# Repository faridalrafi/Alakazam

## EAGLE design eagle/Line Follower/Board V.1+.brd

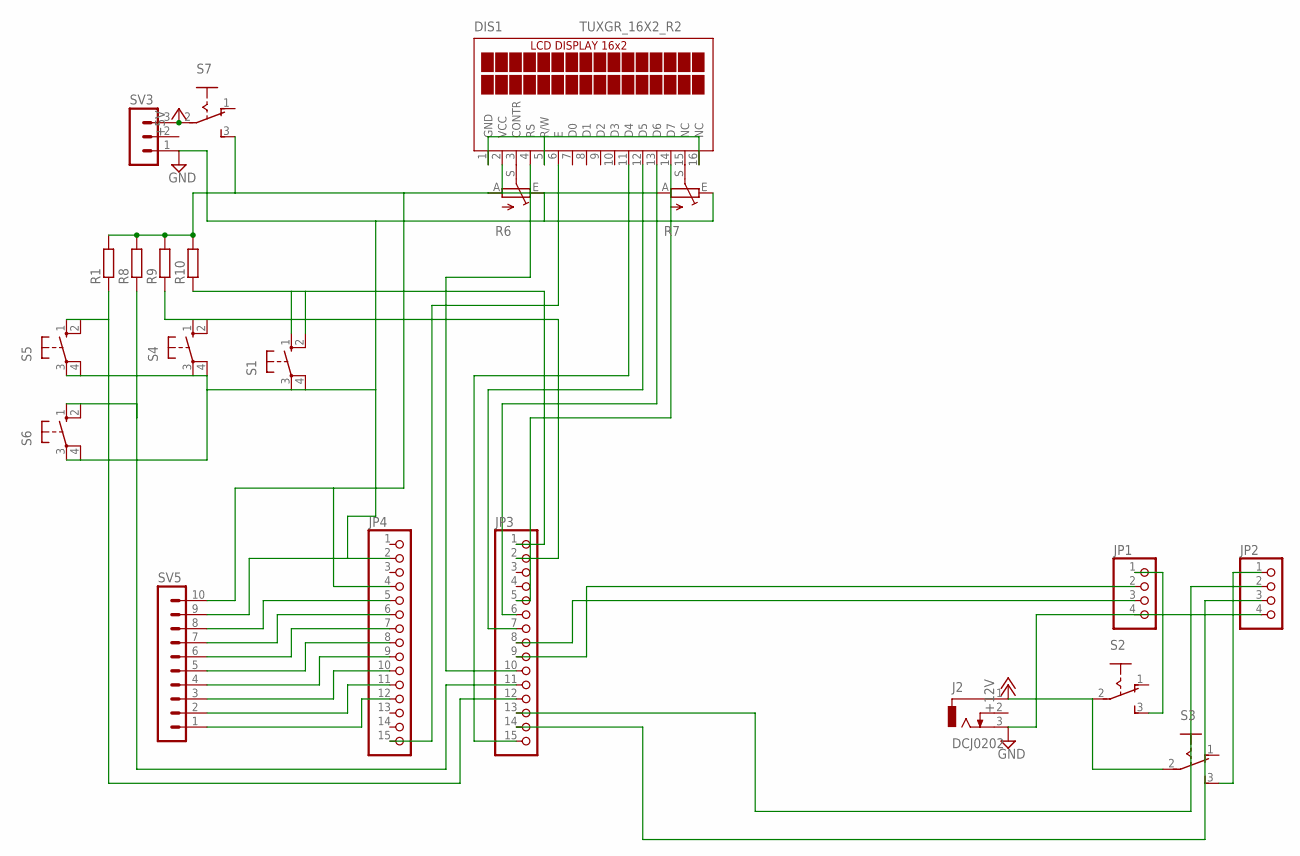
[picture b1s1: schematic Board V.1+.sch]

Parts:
DIS1: TUXGR_16X2_R2
J2: DCJ0202
JP1, JP2: PINHD-1X4; 1X04
JP3, JP4: PINHD-1X15; 1X15
R1, R8, R9, R10: R-EU_0204/7; 0204/7
R6, R7: TRIM_EU-B25P; B25P
S1, S4, S5, S6: 10-XX; B3F-10XX
S2, S3, S7: 255SB
SV3: MA03-1
SV5: MA10-1

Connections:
+5V: S7.2, SV3.3
+5V2: DIS1.2 (VCC), JP4.4, R1.2, R6.A, R7.A, R8.2, R9.2, R10.2, S7.3 (S), SV5.10
+12V: J2.1, S2.2, S3.2
GND: J2.3, JP1.4, JP2.4, JP4.2, R6.E, R7.E, S1.3, S1.4 (P1), S4.3, S4.4 (P1), S5.3, S5.4 (P1), S6.3, S6.4 (P1), SV3.1, SV5.9
unnamed: JP1.1, S2.3 (S)
unnamed: JP2.1, S3.3 (S)
unnamed: JP1.3, JP3.8
unnamed: JP1.2, JP3.9
unnamed: JP3.1, R10.1, S1.1 (S), S1.2 (S1)
unnamed: DIS1.15 (NC), R7.S
unnamed: JP2.2, JP3.13
unnamed: DIS1.4 (RS), JP3.10
unnamed: DIS1.3 (CONTR), R6.S
unnamed: DIS1.6 (E), JP4.15
unnamed: DIS1.11 (D4), JP3.15
unnamed: JP4.5, SV5.8
unnamed: JP4.6, SV5.7
unnamed: JP4.7, SV5.6
unnamed: JP4.8, SV5.5
unnamed: JP4.9, SV5.4
unnamed: DIS1.12 (D5), JP3.7
unnamed: DIS1.13 (D6), JP3.6
unnamed: DIS1.14 (D7), JP3.5
unnamed: JP3.2, R9.1, S4.1 (S), S4.2 (S1)
unnamed: JP3.11, R8.1, S6.1 (S), S6.2 (S1)
unnamed: JP3.12, R1.1, S5.1 (S), S5.2 (S1)
unnamed: DIS1.1 (GND), DIS1.5 (R/W), DIS1.16 (NC)
unnamed: JP2.3, JP3.14
unnamed: JP4.10, SV5.3
unnamed: JP4.11, SV5.2
unnamed: JP4.12, SV5.1

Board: 2 copper layers, 21 parts (1 on the bottom side), 31 nets, no tracks yet.

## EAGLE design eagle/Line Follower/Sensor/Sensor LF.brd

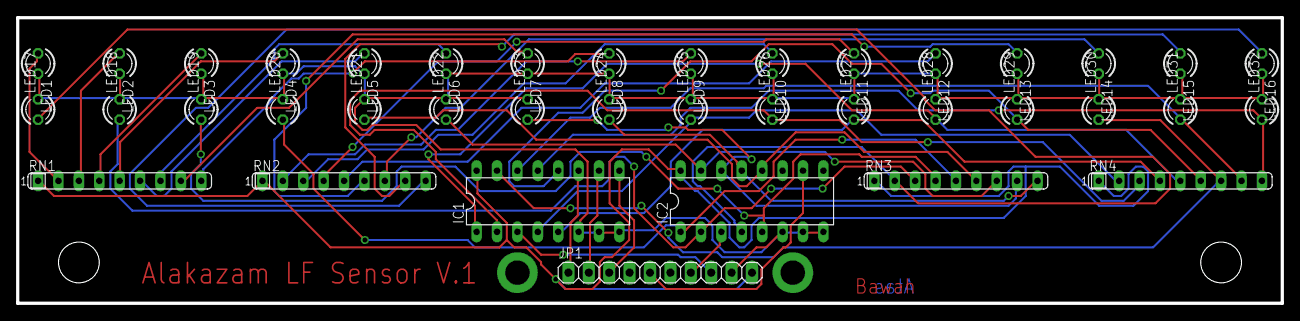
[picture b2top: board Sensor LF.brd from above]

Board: 2 copper layers, 157.5 x 35.6 mm, 39 parts (0 on the bottom side), 42 nets.

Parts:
IC1, IC2: 4051N; DIL16
JP1: 1X10
LED1, LED2, LED3, LED4, LED5, LED6, LED7, LED8, LED9, LED10, LED11, LED12, LED13, LED14, LED15, LED16, LED17, LED18, LED19, LED20, LED21, LED22, LED23, LED24, LED25, LED26, LED27, LED28, LED29, LED30, LED31, LED32: LED3MM
RN1, RN2: 220; SIL9
RN3, RN4: 10K; SIL9

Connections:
+5V: IC1.16, IC2.16, JP1.10, RN1.1, RN2.1, RN3.1, RN4.1
GND: IC1.6, IC1.7, IC1.8, IC2.6, IC2.7, IC2.8, JP1.9, LED1.K, LED2.K, LED3.K, LED4.K, LED5.K, LED6.K, LED7.K, LED8.K, LED9.K, LED10.K, LED11.K, LED12.K, LED13.K, LED14.K, LED15.K, LED16.K, LED17.K, LED18.K, LED19.K, LED20.K, LED21.K, LED22.K, LED23.K, LED24.K, LED25.K, LED26.K, LED27.K, LED28.K, LED29.K, LED30.K, LED31.K, LED32.K
unnamed: IC1.10, JP1.2
unnamed: IC1.9, JP1.3
unnamed: IC2.11, JP1.6
unnamed: IC2.10, JP1.5
unnamed: IC2.9, JP1.4
unnamed: IC2.3, JP1.7
unnamed: LED1.A, RN1.2
unnamed: LED2.A, RN1.3
unnamed: IC2.4, LED17.A, RN3.2
unnamed: IC2.2, LED18.A, RN3.3
unnamed: IC2.5, LED19.A, RN3.4
unnamed: IC2.1, LED20.A, RN3.5
unnamed: IC2.12, LED21.A, RN3.6
unnamed: IC2.15, LED22.A, RN3.7
unnamed: IC2.14, LED23.A, RN3.8
unnamed: IC2.13, LED24.A, RN3.9
unnamed: IC1.4, LED25.A, RN4.2
unnamed: IC1.2, LED26.A, RN4.3
unnamed: IC1.5, LED27.A, RN4.4
unnamed: IC1.1, LED28.A, RN4.5
unnamed: IC1.12, LED29.A, RN4.6
unnamed: IC1.15, LED30.A, RN4.7
unnamed: IC1.14, LED31.A, RN4.8
unnamed: IC1.13, LED32.A, RN4.9
unnamed: LED3.A, RN1.4
unnamed: LED4.A, RN1.5
unnamed: LED5.A, RN1.6
unnamed: LED6.A, RN1.7
unnamed: LED7.A, RN1.8
unnamed: LED8.A, RN1.9
unnamed: LED9.A, RN2.2
unnamed: LED10.A, RN2.3
unnamed: LED11.A, RN2.4
unnamed: LED12.A, RN2.5
unnamed: LED13.A, RN2.6
unnamed: LED14.A, RN2.7
unnamed: LED15.A, RN2.8
unnamed: LED16.A, RN2.9
unnamed: IC1.3, JP1.8
unnamed: IC1.11, JP1.1

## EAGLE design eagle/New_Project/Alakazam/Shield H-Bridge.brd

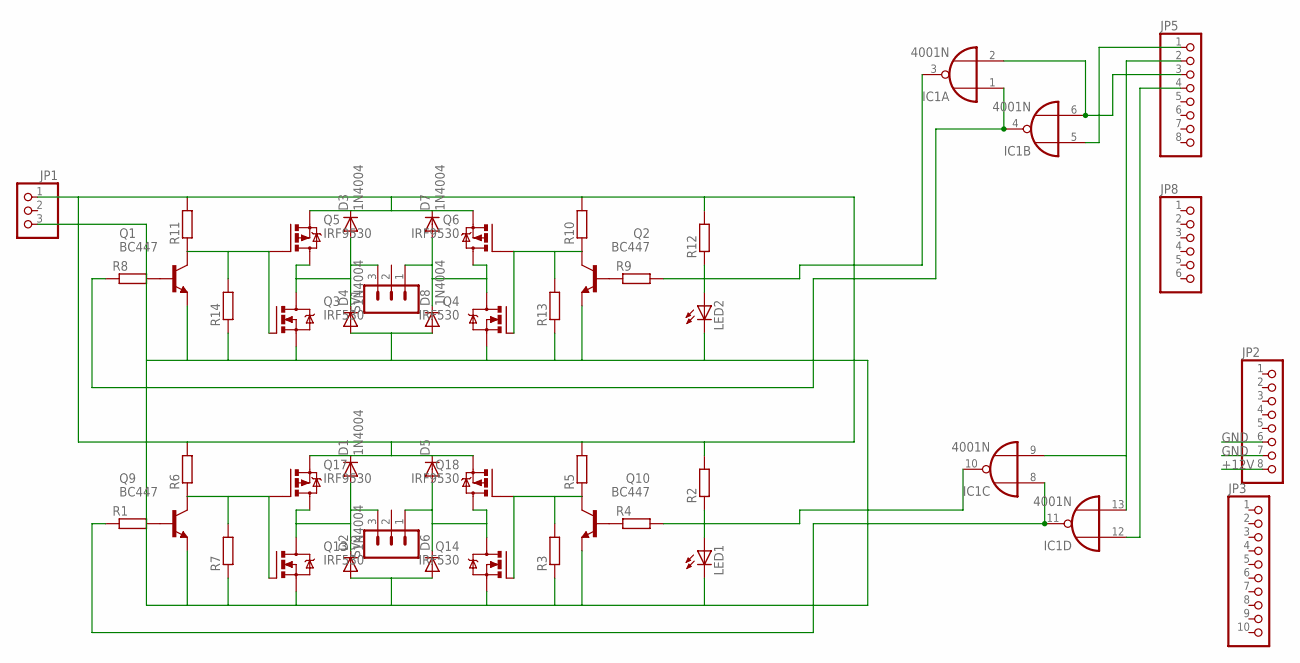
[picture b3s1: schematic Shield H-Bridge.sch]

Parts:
D1, D2, D3, D4, D5, D6, D7, D8: 1N4004; DO41-10
IC1: 4001N; DIL14
JP1: PINHD-1X3; 1X03
JP2, JP5: PINHD-1X8; 1X08
JP3: PINHD-1X10; 1X10
JP8: PINHD-1X6; 1X06
LED1, LED2: LED3MM
Q1, Q2, Q9, Q10: BC447; TO92-EBC
Q3, Q4, Q13, Q14: IRF530; TO220BV
Q5, Q6, Q17, Q18: IRF9530; TO220BV
R1, R4, R5, R6, R8, R9, R10, R11: R-EU_0207/10; 0207/10
R2, R12: R-EU_0204/5; 0204/5
R3, R7, R13, R14: R-EU_0204/7; 0204/7
SV1, SV2: MA03-1

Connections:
+12V: D1.C, D3.C, D5.C, D7.C, JP1.1, JP2.8, Q5.S, Q6.S, Q17.S, Q18.S, R2.2, R5.2, R6.2, R10.2, R11.2, R12.2
GND: D2.A, D4.A, D6.A, D8.A, JP1.3, JP2.6, JP2.7, LED1.K (C), LED2.K (C), Q1.E, Q2.E, Q3.S, Q4.S, Q9.E, Q10.E, Q13.S, Q14.S, R3.1, R7.1, R13.1, R14.1
unnamed: Q9.B, R1.2
unnamed: Q10.B, R4.1
unnamed: D7.A, D8.C, Q4.D, Q6.D, SV1.1
unnamed: IC1.12 (I0), JP5.4
unnamed: D3.A, D4.C, Q3.D, Q5.D, SV1.3
unnamed: Q2.C, Q4.G, Q6.G, R10.1, R13.2
unnamed: D5.A, D6.C, Q14.D, Q18.D, SV2.1
unnamed: D1.A, D2.C, Q13.D, Q17.D, SV2.3
unnamed: LED1.A, R2.1
unnamed: Q1.B, R8.2
unnamed: Q2.B, R9.1
unnamed: Q10.C, Q14.G, Q18.G, R3.2, R5.1
unnamed: Q1.C, Q3.G, Q5.G, R11.1, R14.2
unnamed: LED2.A, R12.1
unnamed: IC1.2 (I1), IC1.6 (I1), JP5.3
unnamed: Q9.C, Q13.G, Q17.G, R6.1, R7.2
unnamed: IC1.9 (I1), IC1.13 (I1), JP5.2
unnamed: IC1.5 (I0), JP5.1
PWM1: IC1.10 (O), R4.2
PWM2: IC1.8 (I0), IC1.11 (O), R1.1
PWM3: IC1.1 (I0), IC1.4 (O), R8.1
PWM4: IC1.3 (O), R9.2
VDD: IC1.14 (VDD)
VSS: IC1.7 (VSS)

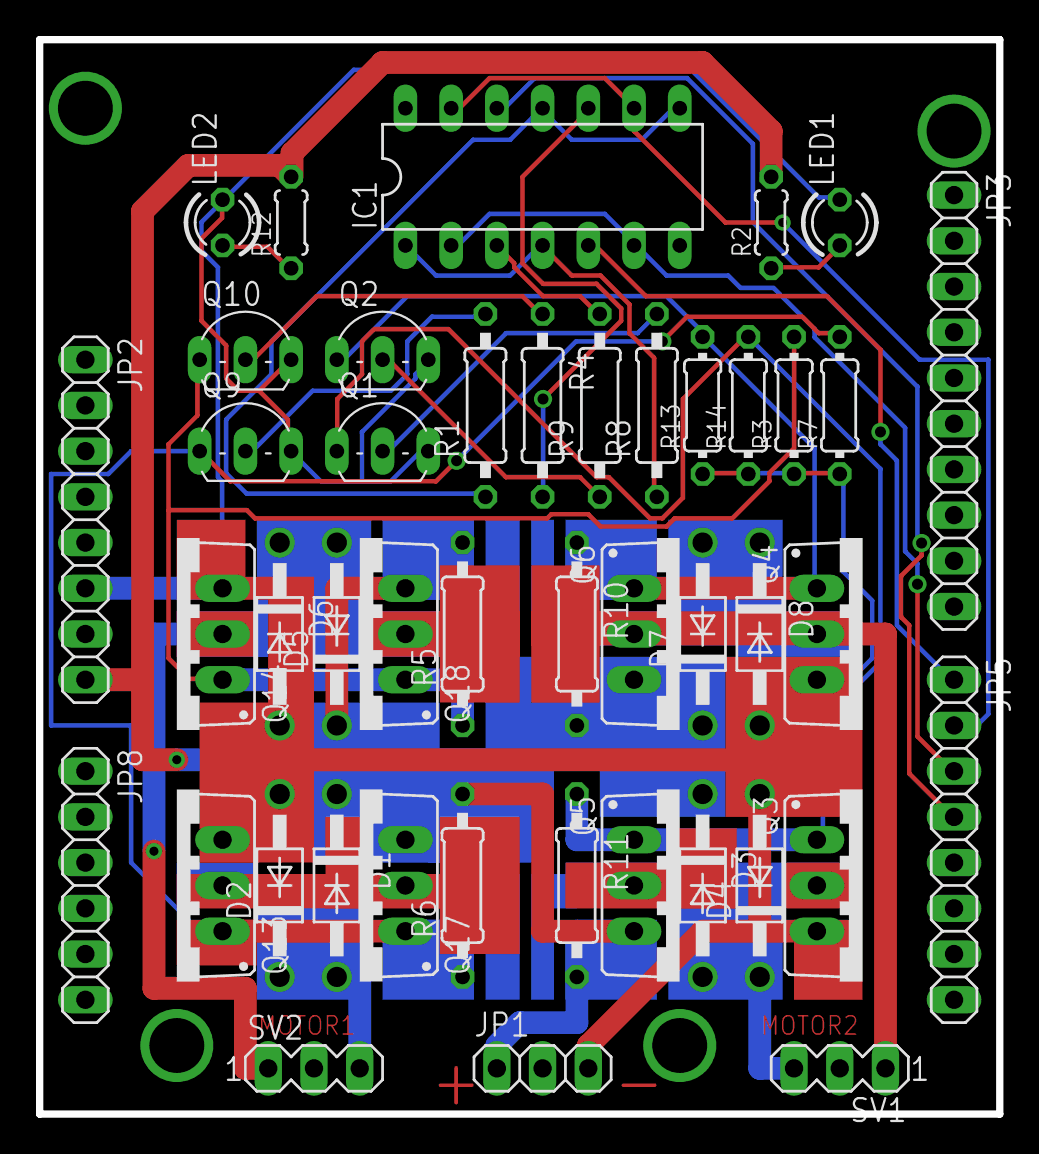
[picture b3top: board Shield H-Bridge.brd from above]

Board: 2 copper layers, 53.3 x 59.7 mm, 44 parts (0 on the bottom side), 24 nets.

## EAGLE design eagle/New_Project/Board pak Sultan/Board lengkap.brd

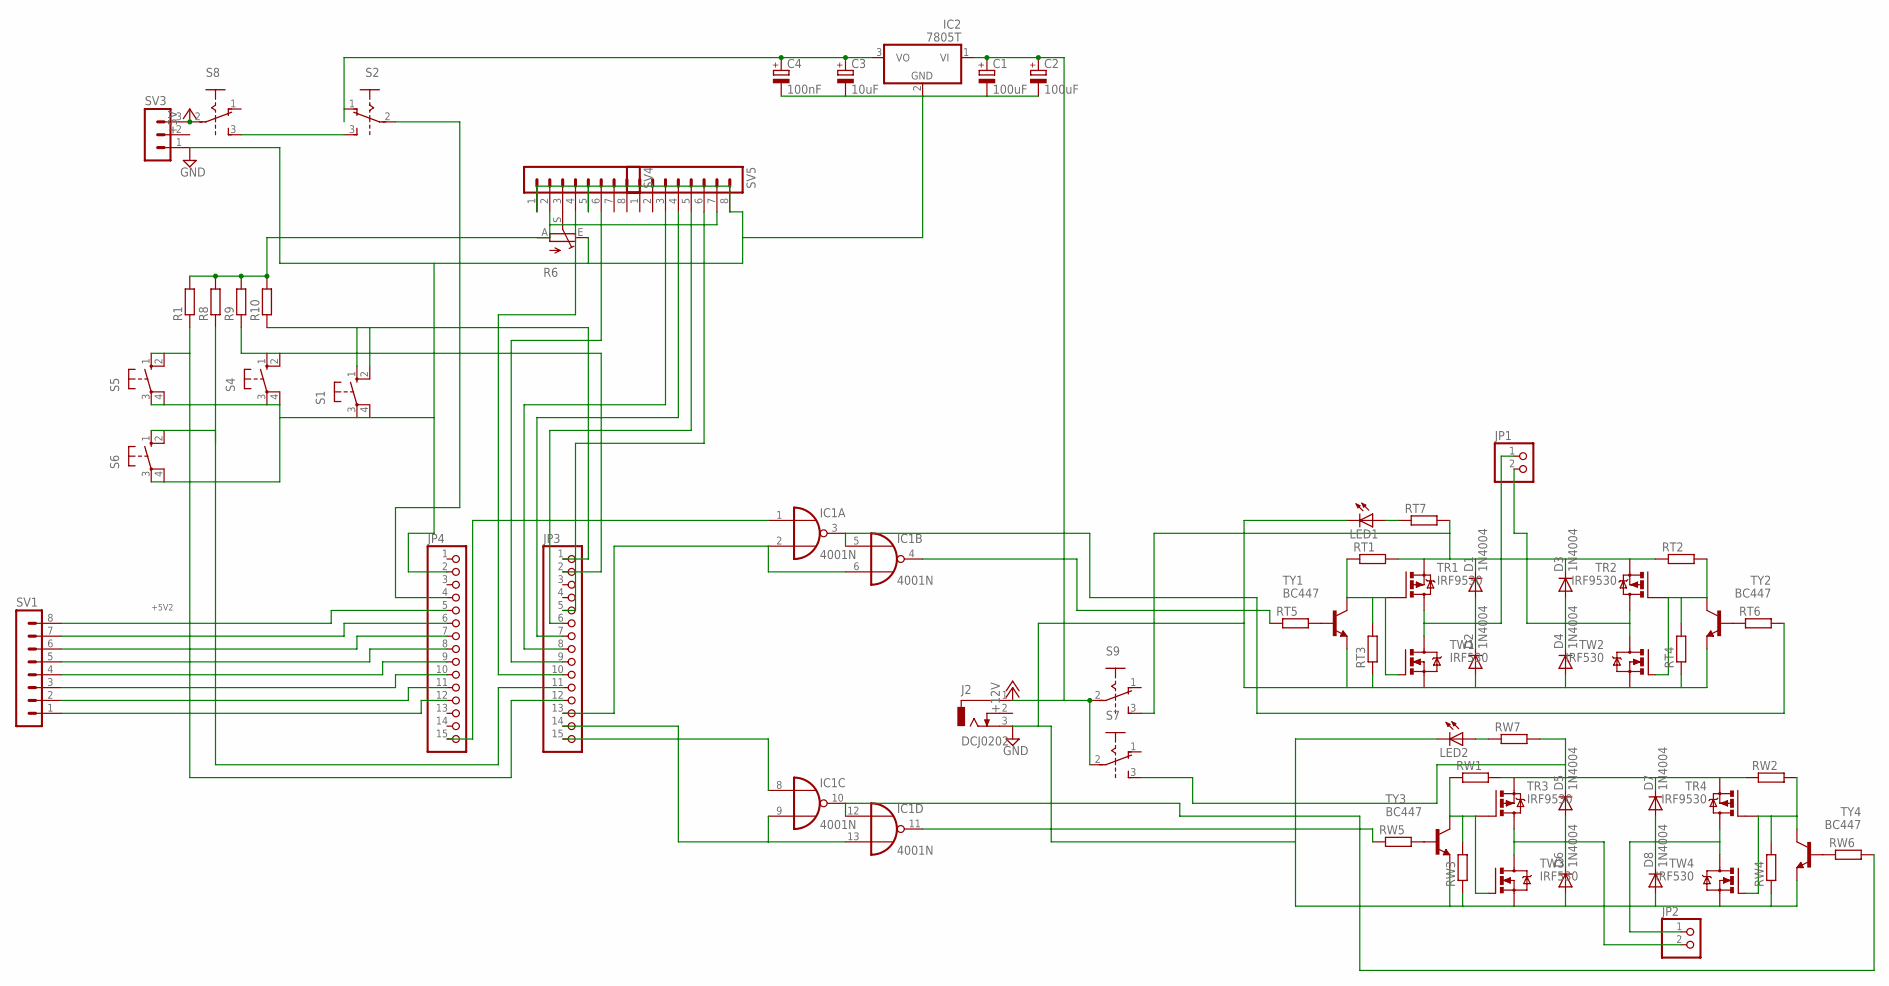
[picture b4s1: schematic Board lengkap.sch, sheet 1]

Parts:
C1, C2: 100uF; E2,5-6
C3: 10uF; E2,5-6
C4: 100nF; E2,5-6
D1, D2, D3, D4, D5, D6, D7, D8: 1N4004; DO41-10
IC1: 4001N; DIL14
IC2: 7805T; TO220H
J2: DCJ0202
JP1, JP2: PINHD-1X2; 1X02
JP3, JP4: PINHD-1X15; 1X15
LED1, LED2: LED5MM
R1, R8, R9, R10: R-EU_0204/7; 0204/7
R6: TRIM_EU-B25P; B25P
RT1, RT2, RT3, RT4, RT5, RT6, RT7: R-EU_0207/7; 0207/7
RW1, RW2, RW3, RW4, RW5, RW6, RW7: R-EU_0207/7; 0207/7
S1, S4, S5, S6: 10-XX; B3F-10XX
S2, S7, S8, S9: A68-A31
SV1, SV4, SV5: MA08-1
SV3: MA03-1
TR1, TR2, TR3, TR4: IRF9530; TO220BV
TW1, TW2, TW3, TW4: IRF530; TO220BV
TY1, TY2, TY3, TY4: BC447; TO92-EBC

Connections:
12V-A: D1.C, D3.C, RT1.2, RT2.1, RT7.2, S9.3 (S), TR1.S, TR2.S
12V-B: D5.C, D7.C, RW1.2, RW2.1, RW7.2, S7.3 (S), TR3.S, TR4.S
+5V: IC1.14 (VDD), S8.2, SV3.3
+5V2: JP4.4, R1.2, R6.A, R8.2, R9.2, R10.2, S2.2, SV4.2, SV5.7
+12V: C1.+, C2.+, IC2.1 (VI), J2.1, S7.2, S9.2
GND: C1.-, C2.-, C3.-, C4.-, D2.A, D4.A, D6.A, D8.A, IC1.7 (VSS), IC2.2 (GND), J2.3, JP4.2, LED1.K (C), LED2.K (C), R6.E, RT3.1, RT4.1, RW3.1, RW4.1, S1.3, S1.4 (P1), S4.3, S4.4 (P1), S5.3, S5.4 (P1), S6.3, S6.4 (P1), SV3.1, SV4.1, SV4.5, SV5.8, TW1.S, TW2.S, TW3.S, TW4.S, TY1.E, TY2.E, TY3.E, TY4.E
unnamed: LED1.A, RT7.1
unnamed: LED2.A, RW7.1
unnamed: IC1.4 (O), RT5.1
unnamed: IC1.1 (I0), JP4.15
unnamed: S2.3 (S), S8.3 (S)
unnamed: JP3.1, R10.1, S1.1 (S), S1.2 (S1)
unnamed: C3.+, C4.+, IC2.3 (VO)
unnamed: RT1.1, RT3.2, TR1.G, TW1.G, TY1.C
unnamed: JP4.8, SV1.5
unnamed: JP3.10, SV4.4
unnamed: IC1.8 (I0), JP3.15
unnamed: R6.S, SV4.3
unnamed: JP3.9, SV4.6
unnamed: JP4.7, SV1.6
unnamed: JP3.8, SV5.3
unnamed: RT5.2, TY1.B
unnamed: RT6.1, TY2.B
unnamed: RT2.2, RT4.2, TR2.G, TW2.G, TY2.C
unnamed: D7.A, D8.C, JP2.1, TR4.D, TW4.D
unnamed: D5.A, D6.C, JP2.2, TR3.D, TW3.D
unnamed: RW2.2, RW4.2, TR4.G, TW4.G, TY4.C
unnamed: JP4.5, SV1.8
unnamed: JP4.6, SV1.7
unnamed: JP4.9, SV1.4
unnamed: JP3.7, SV5.4
unnamed: JP3.6, SV5.5
unnamed: JP3.5, SV5.6
unnamed: RW1.1, RW3.2, TR3.G, TW3.G, TY3.C
unnamed: JP3.2, R9.1, S4.1 (S), S4.2 (S1)
unnamed: JP3.11, R8.1, S6.1 (S), S6.2 (S1)
unnamed: JP3.12, R1.1, S5.1 (S), S5.2 (S1)
unnamed: RW6.1, TY4.B
unnamed: RW5.2, TY3.B
unnamed: IC1.2 (I1), IC1.6 (I1), JP3.13
unnamed: JP4.12, SV1.1
unnamed: IC1.9 (I1), IC1.13 (I1), JP3.14
unnamed: JP4.10, SV1.3
unnamed: JP4.11, SV1.2
unnamed: D1.A, D2.C, JP1.1, TR1.D, TW1.D
unnamed: D3.A, D4.C, JP1.2, TR2.D, TW2.D
unnamed: IC1.3 (O), IC1.5 (I0), RT6.2
unnamed: IC1.10 (O), IC1.12 (I0), RW6.2
unnamed: IC1.11 (O), RW5.1

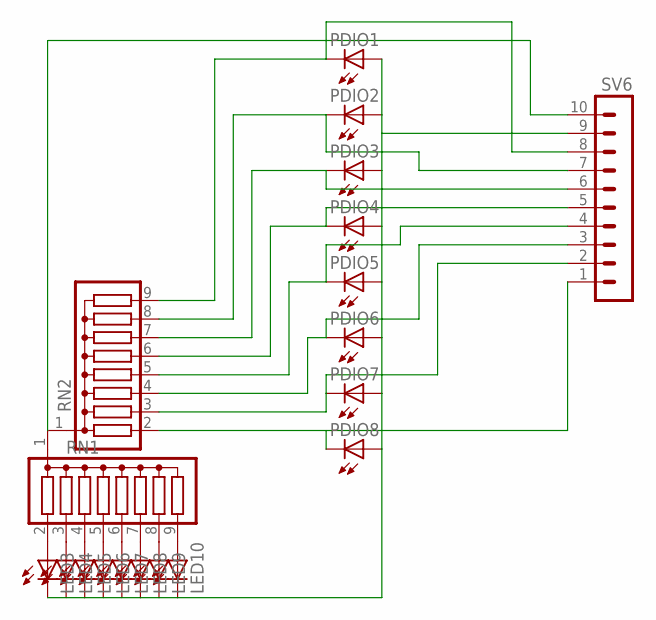
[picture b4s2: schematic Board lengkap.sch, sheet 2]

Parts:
LED3, LED4, LED5, LED6, LED7, LED8, LED9, LED10: LED3MM
PDIO1, PDIO2, PDIO3, PDIO4, PDIO5, PDIO6, PDIO7, PDIO8: LED3MM
RN1, RN2: G08R; SIL9
SV6: MA10-1

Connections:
GND1: LED3.K (C), LED4.K (C), LED5.K (C), LED6.K (C), LED7.K (C), LED8.K (C), LED9.K (C), LED10.K (C), PDIO1.A, PDIO2.A, PDIO3.A, PDIO4.A, PDIO5.A, PDIO6.A, PDIO7.A, PDIO8.A, SV6.9
unnamed: LED3.A, RN1.2
unnamed: LED4.A, RN1.3
unnamed: LED5.A, RN1.4
unnamed: LED6.A, RN1.5
unnamed: LED7.A, RN1.6
unnamed: LED8.A, RN1.7
unnamed: LED9.A, RN1.8
unnamed: LED10.A, RN1.9
unnamed: PDIO8.K (C), RN2.2, SV6.1
unnamed: PDIO6.K (C), RN2.4, SV6.3
unnamed: PDIO3.K (C), RN2.7, SV6.6
unnamed: PDIO2.K (C), RN2.8, SV6.7
unnamed: PDIO7.K (C), RN2.3, SV6.2
unnamed: PDIO5.K (C), RN2.5, SV6.4
unnamed: PDIO4.K (C), RN2.6, SV6.5
unnamed: PDIO1.K (C), RN2.9, SV6.8
VCC1: RN1.1, RN2.1, SV6.10

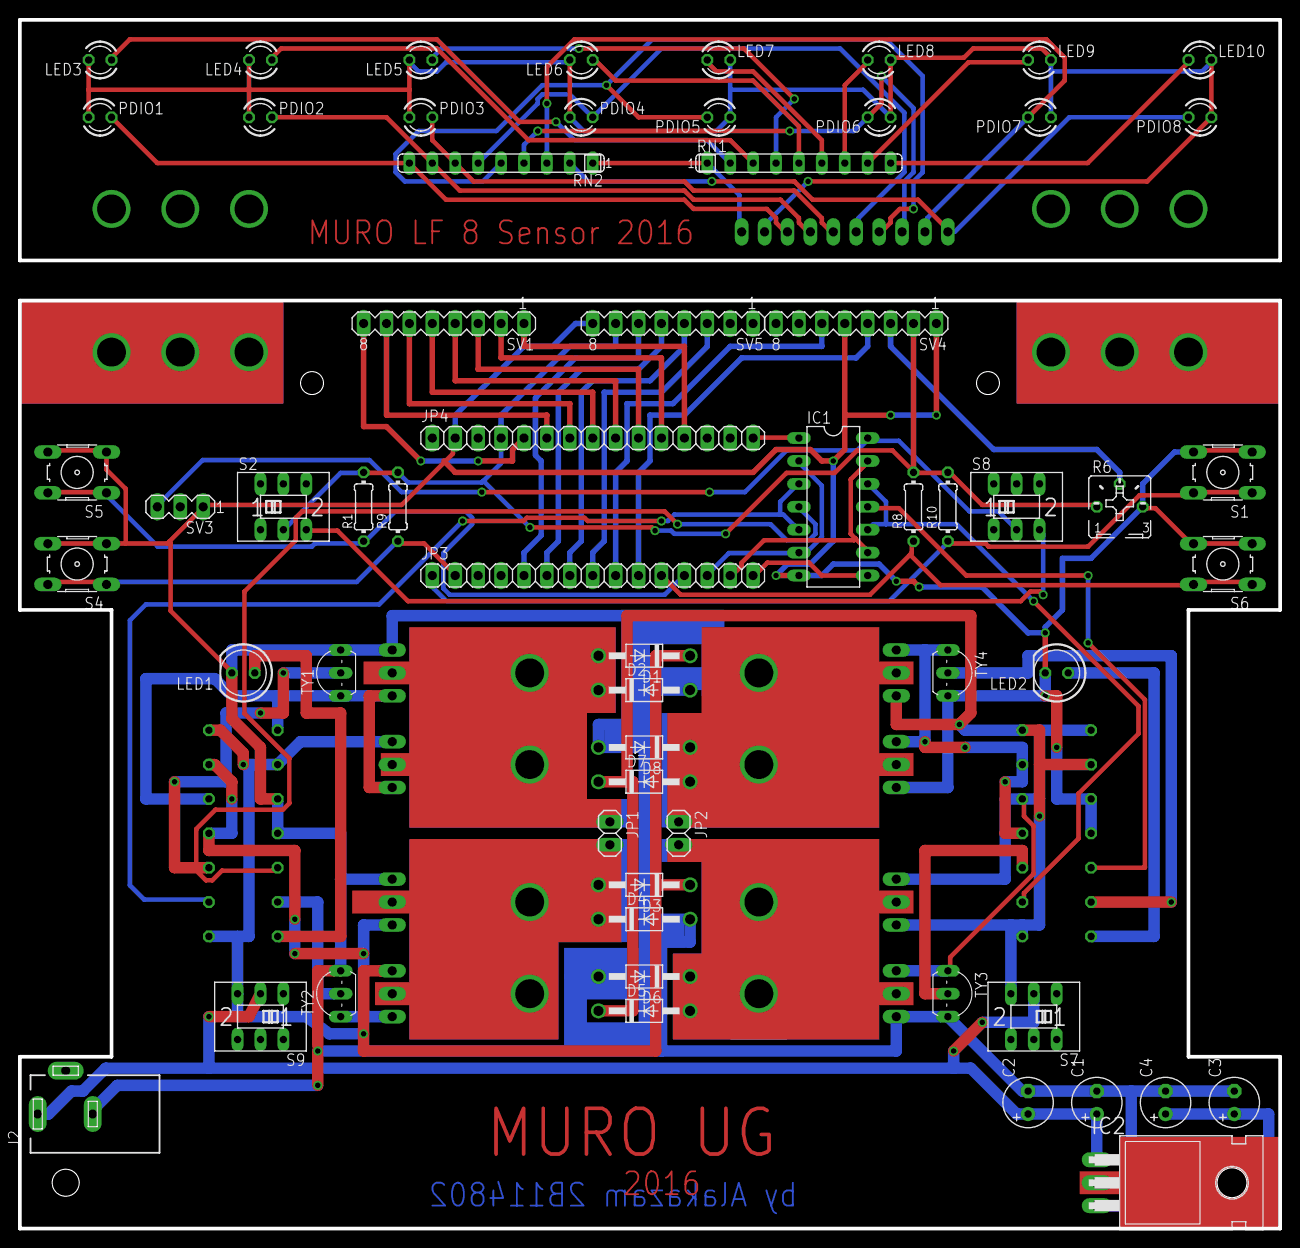
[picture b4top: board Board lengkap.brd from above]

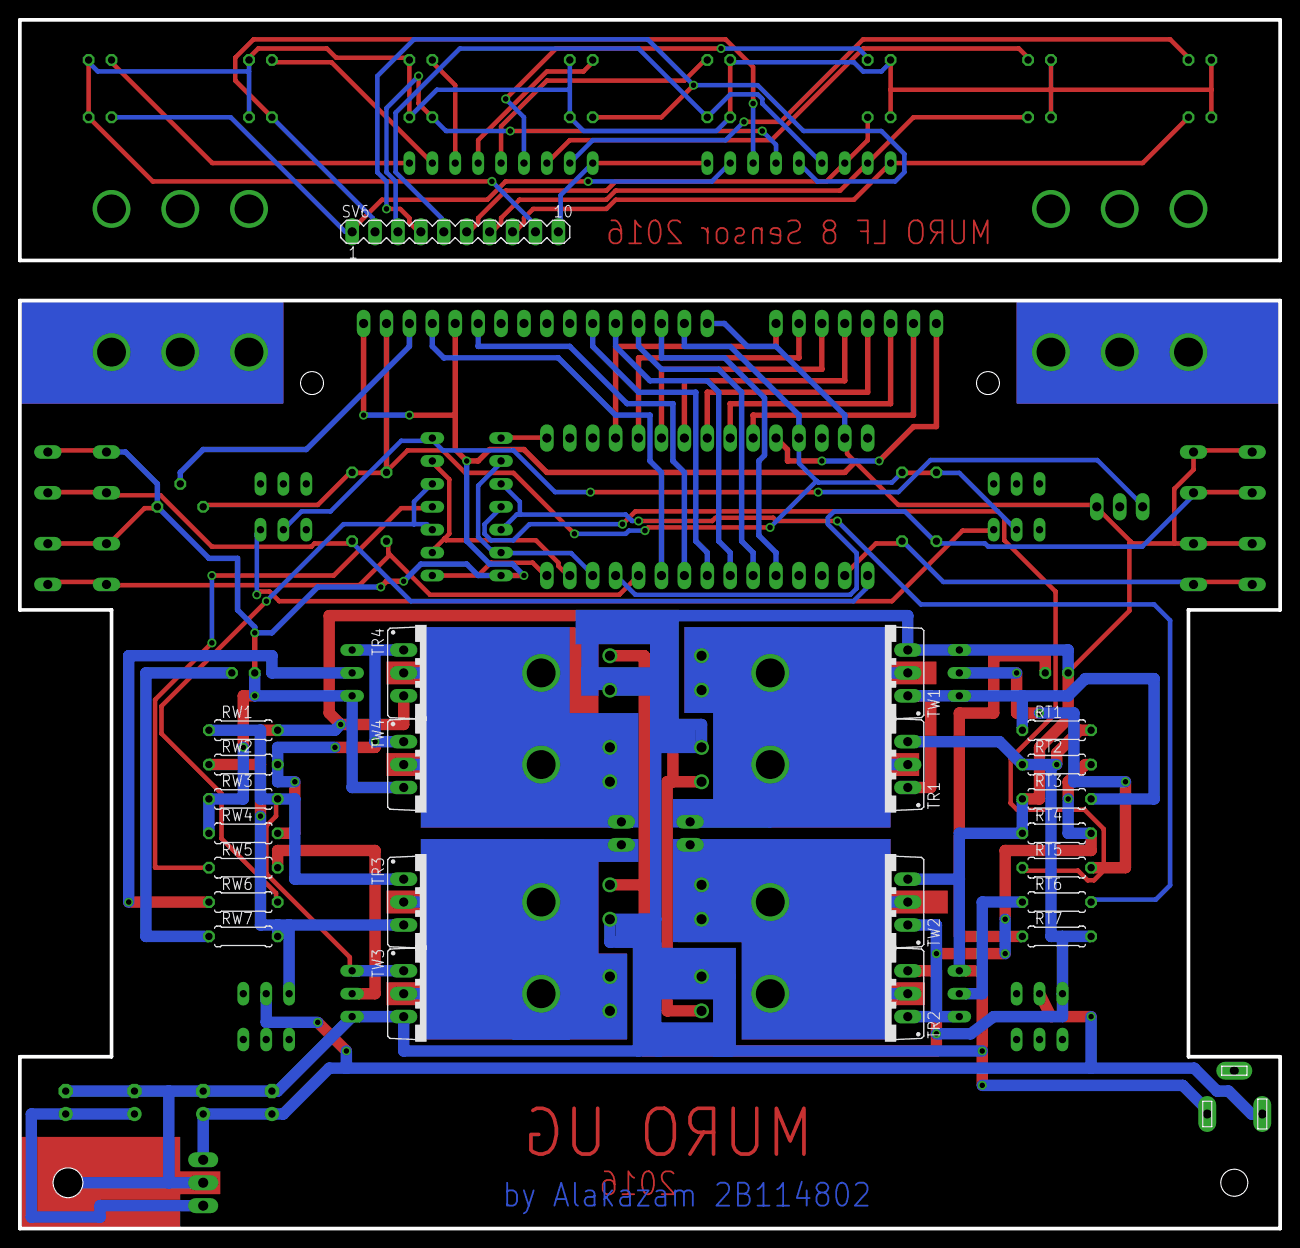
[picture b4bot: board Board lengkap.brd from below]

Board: 2 copper layers, 139.7 x 134.0 mm, 83 parts (23 on the bottom side), 67 nets.

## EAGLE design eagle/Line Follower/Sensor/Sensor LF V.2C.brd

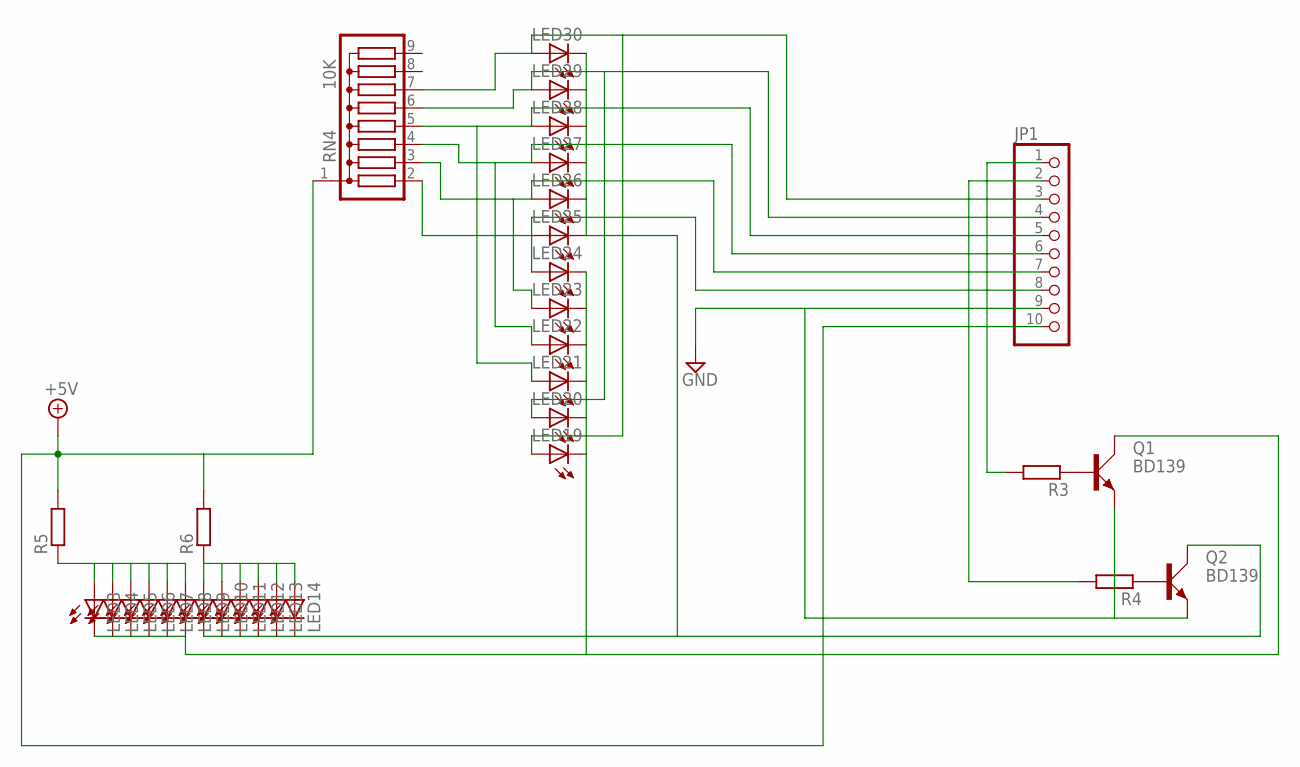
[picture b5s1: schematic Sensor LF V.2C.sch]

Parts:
JP1: PINHD-1X10; 1X10
LED3, LED4, LED5, LED6, LED7, LED8, LED9, LED10, LED11, LED12, LED13, LED14, LED19, LED20, LED21, LED22, LED23, LED24, LED25, LED26, LED27, LED28, LED29, LED30: LED3MM
Q1, Q2: BD139; TO126AV
R3, R4, R5, R6: R-EU_0204/7; 0204/7
RN4: 10K; SIL9

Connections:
+5V: JP1.10, R5.2, R6.2, RN4.1
GND: JP1.9, Q1.E, Q2.E
unnamed: Q2.B, R4.1
unnamed: LED9.K (C), LED10.K (C), LED11.K (C), LED12.K (C), LED13.K (C), LED14.K (C), LED25.K (C), LED26.K (C), LED27.K (C), LED28.K (C), LED29.K (C), LED30.K (C), Q2.C
unnamed: LED3.K (C), LED4.K (C), LED5.K (C), LED6.K (C), LED7.K (C), LED8.K (C), LED19.K (C), LED20.K (C), LED21.K (C), LED22.K (C), LED23.K (C), LED24.K (C), Q1.C
unnamed: JP1.2, R4.2
unnamed: JP1.1, R3.2
unnamed: JP1.8, LED24.A, LED25.A, RN4.2
unnamed: JP1.7, LED23.A, LED26.A, RN4.3
unnamed: JP1.6, LED22.A, LED27.A, RN4.4
unnamed: JP1.5, LED21.A, LED28.A, RN4.5
unnamed: JP1.4, LED20.A, LED29.A, RN4.6
unnamed: JP1.3, LED19.A, LED30.A, RN4.7
unnamed: Q1.B, R3.1
unnamed: LED3.A, LED4.A, LED5.A, LED6.A, LED7.A, LED8.A, R5.1
unnamed: LED9.A, LED10.A, LED11.A, LED12.A, LED13.A, LED14.A, R6.1

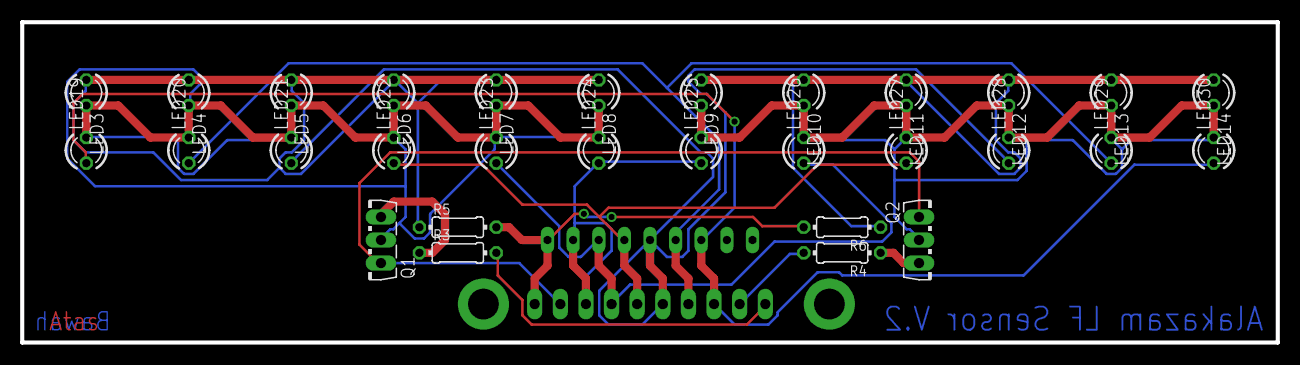
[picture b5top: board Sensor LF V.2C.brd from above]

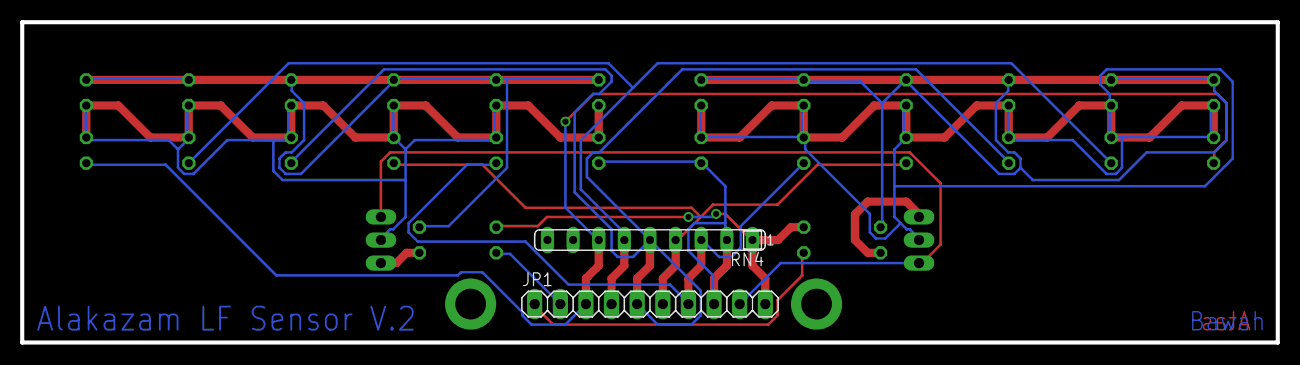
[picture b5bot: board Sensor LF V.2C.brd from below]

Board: 2 copper layers, 124.5 x 31.8 mm, 32 parts (2 on the bottom side), 16 nets.

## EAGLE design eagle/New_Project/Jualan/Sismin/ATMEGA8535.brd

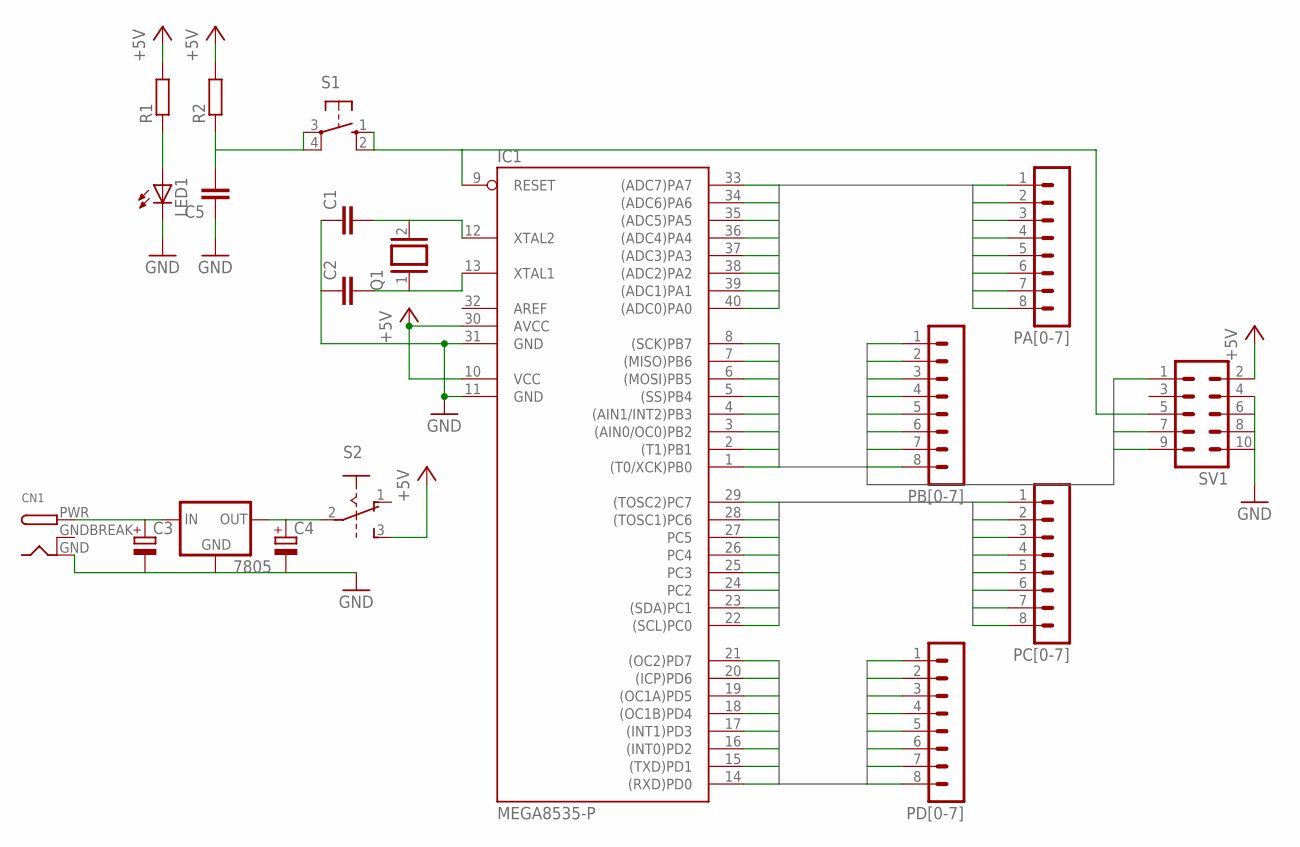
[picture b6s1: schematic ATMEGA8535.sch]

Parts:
7805: 78XXL
C1, C2: C-EU025-025X050; C025-025X050
C3, C4: CPOL-EUE2.5-5; E2,5-5
C5: C-EU050-025X075; C050-025X075
CN1: DCBARRELPTH; DCJACK_2MM_PTH
IC1: MEGA8535-P; DIL40
LED1: LED5MM
PA[0-7]: MA08-1
PB[0-7]: MA08-1
PC[0-7]: MA08-1
PD[0-7]: MA08-1
Q1: XTAL/S; QS
R1, R2: R-EU_0207/7; 0207/7
S1: 10-XX; B3F-10XX
S2: A68-A31
SV1: MA05-2

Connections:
+5V: IC1.10 (VCC), IC1.30 (AVCC), R1.2, R2.2, S2.3 (S), SV1.2
GND: 7805.GND, C1.1, C2.1, C3.-, C4.-, C5.1, CN1.GND, IC1.11 (GND), IC1.31 (GND), LED1.K (C), SV1.4, SV1.6, SV1.8, SV1.10
GNDBREAK: CN1.GNDBREAK
unnamed: IC1.9 (RESET), S1.1 (S), S1.2 (S1), SV1.5
unnamed: C2.2, IC1.13 (XTAL1), Q1.1
unnamed: C1.2, IC1.12 (XTAL2), Q1.2
unnamed: 7805.IN, C3.+, CN1.PWR
unnamed: LED1.A, R1.1
unnamed: 7805.OUT, C4.+, S2.2
unnamed: C5.2, R2.1, S1.3, S1.4 (P1)
PA0: IC1.40 ((ADC0)PA0), PA[0-7].1
PA1: IC1.39 ((ADC1)PA1), PA[0-7].2
PA2: IC1.38 ((ADC2)PA2), PA[0-7].3
PA3: IC1.37 ((ADC3)PA3), PA[0-7].4
PA4: IC1.36 ((ADC4)PA4), PA[0-7].5
PA5: IC1.35 ((ADC5)PA5), PA[0-7].6
PA6: IC1.34 ((ADC6)PA6), PA[0-7].7
PA7: IC1.33 ((ADC7)PA7), PA[0-7].8
PB0: IC1.1 ((T0/XCK)PB0), PB[0-7].1
PB1: IC1.2 ((T1)PB1), PB[0-7].2
PB2: IC1.3 ((AIN0/OC0)PB2), PB[0-7].3
PB3: IC1.4 ((AIN1/INT2)PB3), PB[0-7].4
PB4: IC1.5 ((SS)PB4), PB[0-7].5
PB5: IC1.6 ((MOSI)PB5), PB[0-7].6, SV1.1
PB6: IC1.7 ((MISO)PB6), PB[0-7].7, SV1.9
PB7: IC1.8 ((SCK)PB7), PB[0-7].8, SV1.7
PC0: IC1.22 ((SCL)PC0), PC[0-7].1
PC1: IC1.23 ((SDA)PC1), PC[0-7].2
PC2: IC1.24 (PC2), PC[0-7].3
PC3: IC1.25 (PC3), PC[0-7].4
PC4: IC1.26 (PC4), PC[0-7].5
PC5: IC1.27 (PC5), PC[0-7].6
PC6: IC1.28 ((TOSC1)PC6), PC[0-7].7
PC7: IC1.29 ((TOSC2)PC7), PC[0-7].8
PD0: IC1.14 ((RXD)PD0), PD[0-7].1
PD1: IC1.15 ((TXD)PD1), PD[0-7].2
PD2: IC1.16 ((INT0)PD2), PD[0-7].3
PD3: IC1.17 ((INT1)PD3), PD[0-7].4
PD4: IC1.18 ((OC1B)PD4), PD[0-7].5
PD5: IC1.19 ((OC1A)PD5), PD[0-7].6
PD6: IC1.20 ((ICP)PD6), PD[0-7].7
PD7: IC1.21 ((OC2)PD7), PD[0-7].8

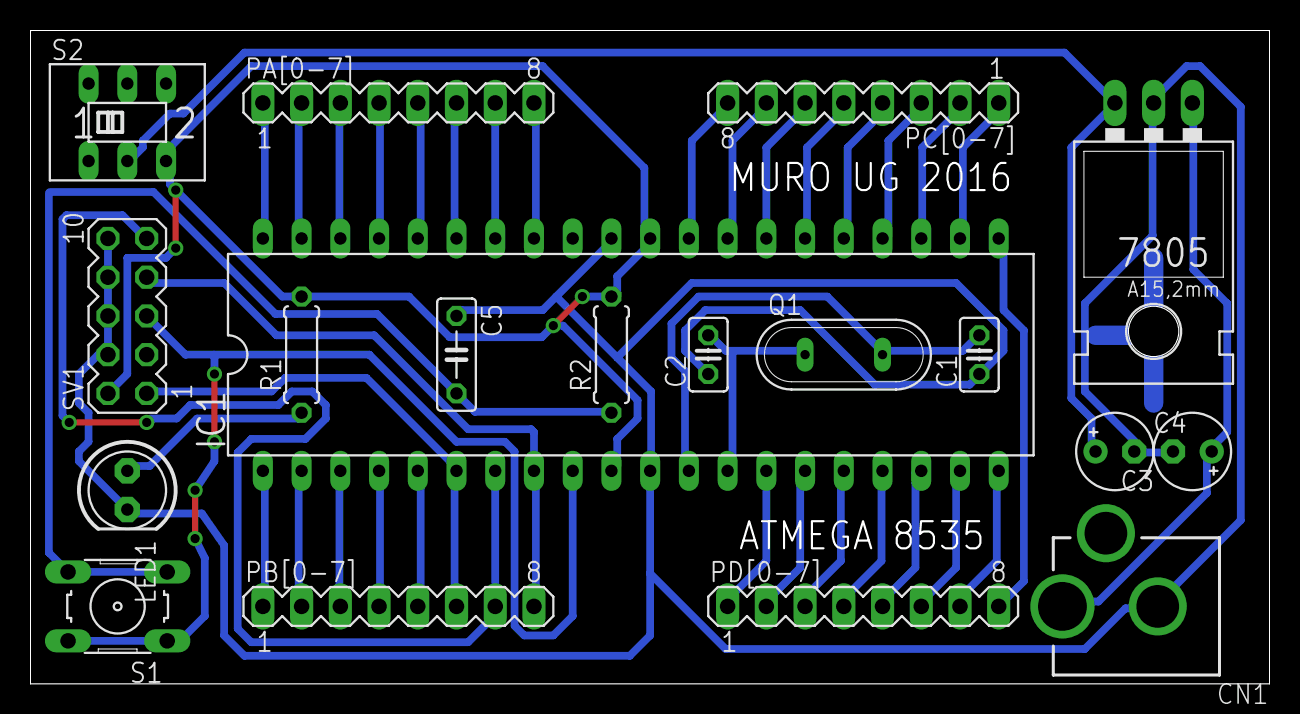
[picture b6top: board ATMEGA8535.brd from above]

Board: 2 copper layers, 81.3 x 42.9 mm, 19 parts (0 on the bottom side), 41 nets.

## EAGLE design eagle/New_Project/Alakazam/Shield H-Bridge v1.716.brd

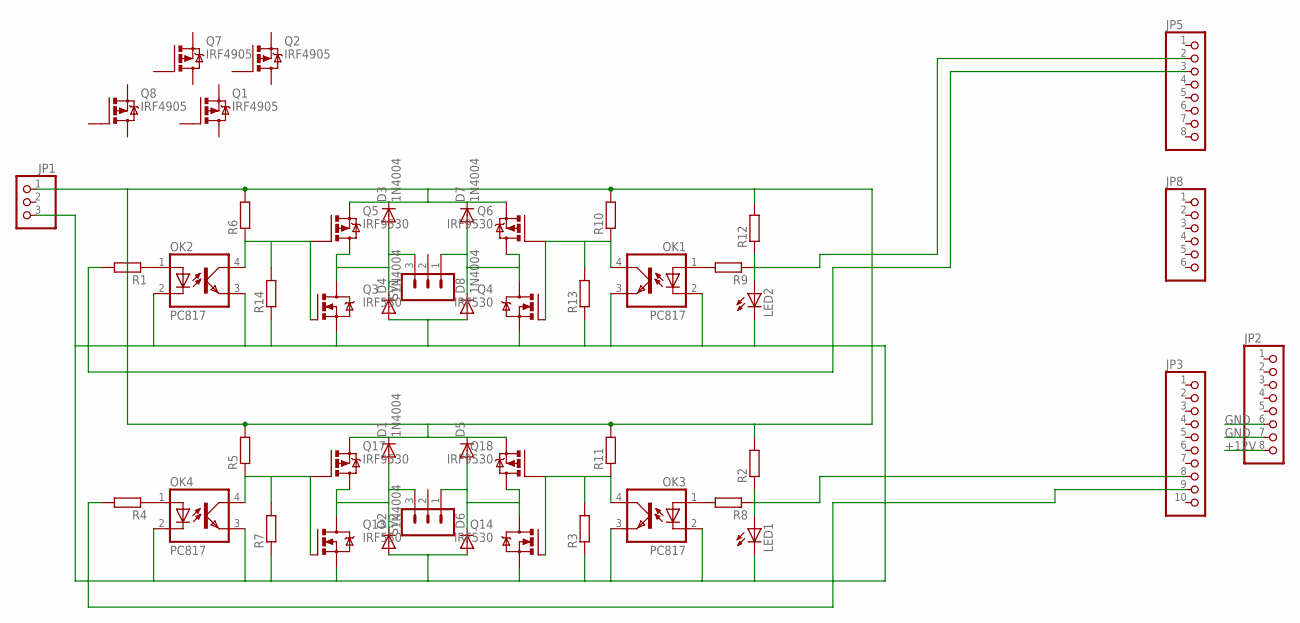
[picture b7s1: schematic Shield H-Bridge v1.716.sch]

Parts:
D1, D2, D3, D4, D5, D6, D7, D8: 1N4004; DO41-10
JP1: PINHD-1X3; 1X03
JP2, JP5: PINHD-1X8; 1X08
JP3: PINHD-1X10; 1X10
JP8: PINHD-1X6; 1X06
LED1, LED2: LED3MM
OK1, OK2, OK3, OK4: PC817; DIL04
Q1, Q2, Q7, Q8: IRF4905; TO220BH
Q3, Q4, Q13, Q14: IRF530; TO220BV
Q5, Q6, Q17, Q18: IRF9530; TO220BV
R1, R3, R4, R5, R6, R7, R8, R9, R10, R11, R13, R14: R-EU_0204/7; 0204/7
R2, R12: R-EU_0204/5; 0204/5
SV1, SV2: MA03-1

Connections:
+12V: D1.C, D3.C, D5.C, D7.C, JP1.1, JP2.8, Q5.S, Q6.S, Q17.S, Q18.S, R2.2, R5.2, R6.2, R10.2, R11.2, R12.2
GND: D2.A, D4.A, D6.A, D8.A, JP1.3, JP2.6, JP2.7, LED1.K (C), LED2.K (C), OK1.2 (C), OK1.3 (EMIT), OK2.2 (C), OK2.3 (EMIT), OK3.2 (C), OK3.3 (EMIT), OK4.2 (C), OK4.3 (EMIT), Q3.S, Q4.S, Q13.S, Q14.S, R3.1, R7.1, R13.1, R14.1
unnamed: OK2.1 (A), R1.1
unnamed: OK4.1 (A), R4.1
unnamed: D7.A, D8.C, Q4.D, Q6.D, SV1.1
unnamed: D3.A, D4.C, Q3.D, Q5.D, SV1.3
unnamed: OK1.4 (COL), Q4.G, Q6.G, R10.1, R13.2
unnamed: D5.A, D6.C, Q14.D, Q18.D, SV2.1
unnamed: D1.A, D2.C, Q13.D, Q17.D, SV2.3
unnamed: LED1.A, R2.1
unnamed: OK3.1 (A), R8.2
unnamed: OK1.1 (A), R9.2
unnamed: OK3.4 (COL), Q14.G, Q18.G, R3.2, R11.1
unnamed: OK2.4 (COL), Q3.G, Q5.G, R6.1, R14.2
unnamed: LED2.A, R12.1
unnamed: OK4.4 (COL), Q13.G, Q17.G, R5.1, R7.2
PWM1: JP3.8, R8.1
PWM1A: JP5.2, R9.1
PWM1B: JP5.3, R1.2
PWM2: JP3.9, R4.2

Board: 2 copper layers, 47 parts (0 on the bottom side), 20 nets, no tracks yet.
